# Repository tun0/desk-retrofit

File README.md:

# Jysk Slangerup standing desk — smart drive retrofit

Reverse engineering notes, design decisions and firmware for replacing the
control of a **Jysk Slangerup** electric height-adjustable desk.

The original complaint: the up/down buttons switch the motor on at full
voltage, so the desk jolts into motion. The goal is soft start/stop under
programmatic control, with height presets as a later phase.

This document is the project's memory. It records not just the final design
but the measurements it rests on, the alternatives considered, and — deliberately —
the wrong turns, because several conclusions here are only correct in light of
an earlier mistake.

---

## 1. The desk as found

### 1.1 Documented facts

From the JYSK manual (rev. 1, 22.06.2022; item numbers 3601130, 3601131,
75668001, 75672001, C123681):

| Property | Value |
|---|---|
| Height range | 68–118 cm |
| Max load | 40 kg |
| Speed | ~25 mm/s, load dependent |
| Duty cycle | 10% at 50% max load, or 2 min continuous |
| Operation | Micro switches |
| Anti-collision | **Not listed** (JYSK's SVANEKE model does advertise it) |
| Manufacturer of record | 2-connect ApS, Ikast, Denmark |

Essentially nothing else is publicly documented. 2-connect is a furniture
trading and sourcing company rather than an electronics designer, so they are
the CE-responsible party and the parts are unbranded OEM. There is no control
box model number, no wiring diagram, no service manual, no aftermarket
replacement. The Machinery Directive technical file is only available to
national market-surveillance authorities, not the public.

**Conclusion: everything below was measured, not looked up.**

### 1.2 Physical layout

- **Single motor**, permanently attached to one leg, driving the second leg
  through a shaft. Both columns are mechanically locked together, so one
  position measurement is authoritative for the whole desk.
- **No separate control box.** The electronics — such as they are — live in
  the motor housing. Only two cables exist: PSU → motor housing, and a
  4-conductor cable between the motor housing and the handset.
- The handset enclosure contains two rocker microswitches and nothing else.

### 1.3 Power supply

Label reads:

```
Input:  AC 100-240V  50/60Hz  1.5A
Output: DC 29.0V  1.8A  52.2W
```

The 1.8 A rating turns out to be one of the most important numbers in the
project — see §2.4.

### 1.4 The 4-conductor cable

Terminals on the motor housing, left to right: **red, yellow, white, grey**.

| Conductor | Connects to |
|---|---|
| red | UP rocker only |
| yellow | both rockers |
| white | both rockers |
| grey | DOWN rocker only |

Two shared conductors, one unique conductor per rocker, three terminals per
rocker. That topology is the signature of **two SPDT changeover switches
sharing a common pair** — the minimal H-bridge you can build from two rockers.

### 1.5 The connector

**Molex Mini-Fit Jr., 4.20 mm pitch, 4 circuits, dual row (2x2).**

Identified by caliper, recorded here because the pitch is genuinely awkward to
measure on a moulded housing with recessed cavities, and a first attempt at
buying an extension cable got the wrong part.

Two measurements, and how they combine:

| Measurement | Value |
|---|---|
| Terminal centre-to-centre (pitch), approximate | ~4 mm |
| Outer edge to outer edge across two adjacent cavities | 7.7 mm |

The second is the reliable one — flat outside faces, a longer span, so a
smaller relative error. It equals **one pitch plus one cavity width**:

```
7.7 mm  =  4.2 (pitch)  +  3.5 (cavity)      → Mini-Fit Jr.   ✓
5.4 mm  =  3.0 (pitch)  +  2.4 (cavity)      → Micro-Fit 3.0  ✗
```

Micro-Fit was the initial guess — it is the usual choice for this class of
desk — but it cannot produce a 7.7 mm span. For reference, a Micro-Fit 3.0
dual-row 4-circuit part measures 9.65 mm along the row axis against 6.65 mm
for the 2-circuit version; the 3.00 mm difference is exactly one pitch.

Family identification by pitch, for future reference:

| Pitch | Family | Current/circuit |
|---|---|---|
| 2.00 mm | Milli-Grid | low |
| 2.50 mm | Nano-Fit | ~6.5 A |
| 3.00 mm | Micro-Fit 3.0 | 5.0 A |
| 3.50 mm | Ultra-Fit | ~9 A |
| **4.20 mm** | **Mini-Fit Jr.** | **9.0 A** |

9 A per circuit is wildly over-specified for 1.8 A — normal for a furniture
OEM buying whatever was cheap and available.

Quick sanity check without calipers: Mini-Fit Jr. *is* the ATX family. The
4-pin 12V CPU plug on any PC power supply is the same connector.

### 1.6 Pinout and polarity

Measured on the **5557 receptacle** — the half with the *movable* thumb latch,
holding female sockets. The 5559 plug has the fixed catch that latch grabs.

```
Receptacle (5557, female sockets, movable latch)
viewed INTO the mating face, latch uppermost:

        ─── latch ───
      ┌───────────────┐
      │  [ 1 ] [ 2 ]  │   motor pair
      │  [ 3 ] [ 4 ]  │   supply pair
      └───────────────┘

  1 = motor          3 = supply +
  2 = motor          4 = supply -
```

The plug, viewed into *its* mating face, is the left-right mirror of this.
Never carry a "left and right" description across from one half to the other.

> **This numbering matches Molex's own, confirmed against the real sales
> drawing (SD-5557-003, also cited in `NETLIST.md` for the symbol pin
> order).** Its "CIRCUIT SIZE LAYOUT" table shows circuits 1/2 in the row
> nearest the latch and 3/4 in the row away from it, viewed into the mating
> face with the latch uppermost — the identical reference frame and
> assignment used above. The housings themselves still carry no legible
> moulded numbers, so this was derived from the drawing's orientation
> reference, not read off the part; a pre-made cable assembly could still
> use different circuit numbers internally, so don't assume one matches
> without checking.

Even with the numbering confirmed, **mark the connector physically**: a
dab of paint or nail varnish on the MOT_A cavity. Then the
mark is the definition and no orientation reasoning is ever needed again. The
housings are polarised, so the box itself cannot be mated the wrong way round.

**Polarity, measured:**

| Applied | Result |
|---|---|
| 3→2 and 4→1 (circuit 2 positive) | **UP** |
| 3→1 and 4→2 (circuit 1 positive) | **DOWN** |

**Naming convention used throughout this project:**

> **MOT_A** is the conductor that must be **positive to raise** the desk =
> circuit 2.
> **MOT_B** = circuit 1.

Defining it this way makes the schematic correct by construction, so the only
project-specific fact to remember is which circuit MOT_A is.

**On wire colours — not needed.** The colours in §1.4 did one job: deriving
the rocker topology. Everything downstream works in circuit numbers, because
the box mates with connectors rather than cutting into the cable, so a
conductor's colour mid-run never comes up. The connector end also carries a
moulded protector sleeve, so the colours are not visible there anyway.

For the record, the mapping is *predicted* but unconfirmed: red is the UP
rocker's common and the rockers rest on NC → V+ (§2.4), so red goes negative
while raising, making **red = circuit 1 (MOT_B)** and **grey = circuit 2
(MOT_A)**. If it is ever wanted, it can be had without opening the handset:
the colours are visible at the motor housing terminals, so continuity from a
housing terminal to a connector pin gives the mapping with the cable still
installed.

**Re-identification recipe.** The numbering is a convenience, not a
dependency — every fact above is re-measurable in about five minutes with
nothing but a multimeter:

| Step | Measurement | Tells you |
|---|---|---|
| 1 | ~2.5 Ω across a pair | that pair is the motor winding |
| 2 | ~29 V across the other pair (powered) | supply pair; DC volts gives + and − |
| 3 | Park at the **bottom** stop, diode mode across the motor pair | the conductor reading ~0.6 V with the **red** probe on it is **MOT_A** (positive raises) |

Step 3 works because at the bottom stop the limit switch is open and its
bypass diode passes only the escape direction, which is up.

---

## 2. Measurements and what each proved

Every measurement below was taken with mains disconnected unless noted.

### 2.1 Which pair is which

With the handset assembly disconnected:

- ~**30 V** across one pair → these are the supply rails, routed up to the handset.
- ~**2.5 Ω** across the other pair → this is the motor winding, routed up and back.

A relay coil at 29 V would read hundreds of ohms to low kilohms. 2.5 Ω can
only be a winding. **This proved the rockers carry full motor current and that
no controller exists anywhere in the desk.**

### 2.2 Isolation

- Supply negative to either winding terminal: **< 1 V**, and **open** on the
  resistance range.
- All conductor combinations open except the 2.5 Ω winding pair.

This ruled out either winding end being permanently tied to a rail — which
would have shorted the supply on the first press of a naive H-bridge retrofit.

### 2.3 End stops

Diode mode across the winding pair, measured at the motor-side terminals:

| Position | Reading |
|---|---|
| Mid-travel | near zero both directions (the winding) |
| Bottom stop | **0.6 V one way, OL the other** |
| Top stop | same behaviour, mirrored |

This identifies **diode-bypassed limit switches** — a normally-closed
microswitch at each end of travel with a diode across it, in **series** with
the winding. At a limit the switch opens: one polarity is blocked entirely,
the other passes through the bypass diode so the desk can drive away from the
stop. Two switches, two diodes, still only two conductors down the leg.

Consequences:
- The desk cannot be driven past either extreme, in hardware, regardless of
  firmware. This is inherited for free by any retrofit.
- Homing is clean: drive down until current collapses to zero. That is the
  switch opening at a repeatable mechanical position.

### 2.4 Rest state and current

With both rockers in neutral, **three of the four contacts read shorted**, to
the **positive** rail. Both rockers sit on their NC contacts, tying both
winding ends to V+. That is dynamic braking, and it explains why the desk
stops as abruptly as it starts.

Locked-rotor current would be 29 V ÷ 2.5 Ω ≈ **11.6 A** — but the supply is
rated 1.8 A. The PSU current-limits long before the winding sees anything like
that. Practical consequences:

- The supply is already acting as the current limiter and, incidentally, as
  the collision protection. Jam the desk and it drops into limit and stalls
  rather than drawing 12 A.
- **Do not casually fit a bigger PSU.** That current limit is load-bearing
  safety on a frame with no other protection, and the motor's thermal rating
  was chosen around it.
- A sanity check supports this: lifting ~60 kg at 25 mm/s is ~15 W mechanical,
  which through a spindle drive lands near 40–50 W electrical. The desk runs
  close to the supply limit under load, which is exactly what the manual's
  "speed depends on load" is describing.

### 2.5 The as-found circuit

```
SW3 (UP rocker, SPDT):
    NC ── V+
    NO ── V−
    COM ── [LIM_top ∥ D_down] ──┐
                                 │
                                (M)
                                 │
SW4 (DOWN rocker, SPDT):         │
    NC ── V+                     │
    NO ── V−                     │
    COM ── [LIM_bot ∥ D_up] ─────┘
```

At rest both rockers sit on NC (→ V+), tying both winding ends to the
positive rail — that's the brake state. Pressing a rocker moves its COM
to NO (→ V−) instead, which is what drives the motor.

Not kept as a separate schematic file — this circuit is fully captured by
the measurements above and the diagram, and the stock wiring is unmodified
in the chosen design (§4).

---

## 3. Design evolution

Four designs were considered in sequence:

| | Design | Outcome |
|---|---|---|
| 3.1 | ESP32 + integrated H-bridge IC | rejected on voltage headroom |
| 3.2 | Relay direction + low-side FET PWM | adopted as the drive topology |
| 3.3 | In-line interceptor with 3-pole transfer relay and automatic fallback | good design, dropped as over-complex |
| 3.4 | **Simple in-line drive** | **chosen** |

> Why each of the first three lost, and what would be worth keeping if any
> were revived, is in **`APPENDIX.md` §5**. Several were reasonable at the time
> and became obsolete only when a later measurement changed the picture.

### 3.4 Simple in-line drive — **CHOSEN**

Same in-line position, no transfer relay, no automatic fallback. The board
owns the winding permanently. Reverting is physical:

```
motor — box — handset      becomes      motor — handset
```

39 components instead of 51. Dropping the transfer also deleted the clamp
diodes: with no transfer relay, 29 V can never appear on the handset
conductors, so there is no transition window to protect against.

---

## 4. The chosen design

Schematic: `desk.kicad_sch` / `.pdf`.

### 4.1 Topology

```
PSU 29V ────────┬── VSW rail
                │
                ├── buck ── +5V ── ESP32
                │
         [K1]───┴────[K2]        two SPDT relays, NC→VSW, NO→MRET
          │           │
          └─ winding ─┘      via limit switches in the leg
                │
              MRET ──[Q5]── GND    low-side PWM
                │
              [D1] freewheel to VSW
```

### 4.2 Relay truth table

`MOT_A` = circuit 2, positive to raise (§1.6). `MOT_B` = circuit 1.

| K1 | K2 | Result |
|---|---|---|
| off | off | both winding ends on VSW → **brake** (matches OEM rest state, and is the boot state) |
| **on** | off | MOT_B to return, MOT_A stays positive → **UP** |
| off | **on** | MOT_A to return, MOT_B stays positive → **DOWN** |
| on | on | both ends on MRET → coast if Q5 off, brake to ground if on |

No combination shorts the supply.

The signal chain therefore runs `DIR_A → U3 → Q3 → K1 = up` and
`DIR_B → U3 → Q4 → K2 = down` (same chip, different gate units - see
NETLIST.md), which is what `relay_up:` and `relay_down:` in
`desk.yaml` are wired to. The current sensor sits in the K1 (MOT_B) leg; either
leg works, since it only needs to be inside the freewheel loop.

### 4.3 The handset

Permanently removed from the motor circuit. The board feeds it **3.3 V** and
reads the rockers as dry contacts — high at rest through the OEM NC contact,
low when pressed. Same cable, same connectors, different job. The tactile
up/down survives alongside the screen.

### 4.4 Current sensing

An **ACS712ELCTR-05B** sits in the motor leg, *not* in the FET return (switched
from the ACS724-5AB this design used earlier — see §6.5/§6.6; same Hall-effect
family, pin-identical, chosen for real stock availability). With low-side
chopping the FET only carries current during the on-time; freewheel current
bypasses it entirely, so a low-side shunt would read a chopped fraction and
need synchronous sampling. In the motor leg the sensor is inside the freewheel
loop and reads true motor current continuously.

Its output is centred at 2.5 V, 185 mV/A (Allegro's own datasheet figure for
this exact part), reaching ~3.4 V at the full ±5 A range - over a comfortable
ADC margin, so R1/R2 (10k/20k) divide it down to a ~2.3 V max. **ISENSE must
be on ADC1** — ADC2 is unusable while WiFi is active.

### 4.5 Failsafe layer

- **Boot state.** R8/R9/R10 hold all three drive lines at "off" before firmware
  runs. These *must* sit on non-strapping GPIOs — on the classic ESP32 avoid
  GPIO0, 2, 12 and 15, since a pull resistor there fights the bootloader and
  GPIO12 pulled high selects the wrong flash voltage. The S3's strapping set
  differs; the principle holds.
- **Watchdog.** A 74HC123 retriggerable monostable (~250 ms) gates all three
  drive lines through a 74HC08. The ESP32 must keep kicking it. This sits
  **downstream of the MCU** deliberately: LEDC PWM keeps running in hardware
  after a firmware hang, so stopping PWM in software is not a safety measure.
- **Sequencing.** Relays change state only with Q5 off and current decayed
  (~50 ms). Switching contacts under a couple of amps of inductive DC is how
  relays weld, and a welded direction relay on a desk is a genuinely bad
  failure. On a watchdog trip this holds automatically: Q5 turns off in
  microseconds while relays take milliseconds to release.
- **Coast is safe.** Loss of drive leaves the desk where it is, because the
  spindle is self-locking. This is why the stock desk isn't dangerous despite
  having no electronics at all.
- **Duty cycle.** Enforce the manual's 10% / 2-minute limit in firmware.
  Thermal damage is the boring failure mode.
- **Travel timeout.** Full range is 500 mm at 25 mm/s, so anything over ~25 s
  of continuous drive is a fault.

---

## 5. Corrections made along the way

Recorded because several later conclusions only make sense in light of these.

1. **"No anti-collision implies no current sensing."** Too quick. If the desk
   had used stall detection at the end stops, it would have needed current
   sensing after all. Resolved by finding passive diode-bypassed limit
   switches — but the inference was unsound until then.
2. **Predicted the wrong diode-test result.** Expected "winding one way, diode
   the other". Wrong: the switch and its bypass sit in *series* with the
   winding, so at a limit one polarity is blocked entirely. The measured
   0.6 V / OL is what the series arrangement predicts.
3. **Recommended BTS7960 / VNH5019 on current headroom alone.** Both are out
   of voltage spec at 29 V (BTS7960: 5.5–27.5 V; VNH5019: 5.5–24 V). They
   survive 40 V+ as absolute maximum, but "probably fine" is not what should
   be holding up a desk.
4. **"Size the bridge for 12 A stall."** Wrong — the PSU current-limits at
   1.8 A, so the winding never sees locked-rotor current. This also reframed
   the supply as the existing collision protection.
5. **"Losing brake removes protection."** Overstated, and inconsistent with
   the self-locking spindle noted elsewhere. The brake does stop-precision
   work, not safety work.
6. **Wired NC to V− in the first `desk_original` schematic.** The measurement
   (three contacts shorted, to the positive rail) says NC → V+. Caught only
   when the netlist was rendered as a connectivity graph; the written note and
   the drawing had disagreed silently.
7. **Ran literal power rails across the schematic sheet.** Intended to remove
   "islands"; produced a picket fence of metre-long ground verticals instead.
   Local GND and rail symbols are the conventional idiom precisely because
   they avoid this. The real problem was that *signals* were labelled rather
   than wired.
8. **Planned an "ESP32 devkit + display" (CYD).** This board lives under the
   desk, not somewhere a display is ever seen, so U1 is a bare
   ESP32-S3-DevKitC instead. A display, if ever wanted, would be a separate
   peripheral mounted on the desk itself, not part of this board.
9. **Specified Q5 as IRLB8721.** Caught by an external review, not by this
   project's own process — the schematic still had it after the part was
   supposedly already swapped. IRLB8721's 30 V VDSS doesn't clear the 29–30 V
   rail once flyback clamping is accounted for; fixed to IRLZ44N (55 V). See
   §6.2.
10. **Assumed hand-wired perfboard was the assembly plan.** Reasoning at the
    time: this design is all through-hole specifically because there's no
    reflow equipment, and a fab-house PCB order felt like overkill for a
    one-off — so point-to-point perfboard wiring, guided by a generated
    wiring table, looked like the natural fit. Reversed once that wiring
    table turned out to need far more jumpers than expected, concentrated
    around locally dense ICs rather than anything structural — a strong
    signal that hand-wiring reliability, not layout, was the actual risk.
    A real 2-layer board (still hand-soldered, still through-hole — see
    §6.5) routes those same nets with zero jumpers once an autorouter can
    place traces on both layers, so it was worth doing even without a
    fab-house order: milled at home from a standard 70×100mm pre-cut
    copper-clad blank instead of ordered or hand-wired. See
    `schematics/desk.kicad_pcb` and its commit history for the design
    itself.
11. **Rejected pcb2gcode on hearsay, never actually tested it.** An earlier
    session ruled it out from other people's reported experiences and
    settled on FlatCAM instead (`schematics/gen/mill.tcl`). Building
    increasingly rigorous isolation-milling verification tooling
    (`verify_isolation.py`) around FlatCAM's output eventually surfaced
    three distinct, confirmed FlatCAM `isolate()` bugs on this board's
    ground-pour-heavy layout — including one (a G-code path-ordering
    detour that silently skips a short loop-closing segment) that isn't
    patchable in general. Trying pcb2gcode directly (after working around
    a stale AUR package — see APPENDIX §7) found it isolates this board
    measurably more completely, with no equivalent defect found. The
    milling pipeline defaulted to pcb2gcode (`make mill`) for a while; the
    FlatCAM pipeline stayed in the repo as an explicit fallback
    (`make mill-flatcam`) since pcb2gcode needed a from-source build. See
    APPENDIX §7 for the full technical investigation.
12. **Assumed a third-party isolation-routing tool was necessary at all.**
    Trying pcb2gcode's own `--voronoi` mode (to clean up some harmless but
    untidy leftover copper) surfaced two more real bugs - one of them an
    actual short, not just cosmetic. That's five confirmed bugs across two
    independent tools' internal polygon-offset algorithms, and zero in
    KiCad's own zone fill. `schematics/gen/custom_isolate.py` generates the
    isolation toolpath directly from that same already-correct KiCad
    boundary (the SVG render `verify_isolation.py` already trusted as
    ground truth) using Shapely/GEOS - a mature, heavily-used library
    specifically because robust polygon offsetting is hard to get right,
    which is exactly where FlatCAM and pcb2gcode's own implementations kept
    failing. Extensive spot-checking (all four mounting holes, a full
    header row, several vias and a thermal-relief pad) found no bugs in it.
    Now the default `make mill`; pcb2gcode and FlatCAM both stay as
    explicit fallbacks (`make mill-pcb2gcode`, `make mill-flatcam`). See
    APPENDIX §7.2 for the full investigation.
13. **`island_removal_mode=Never` on both GND pours, inherited unchanged
    into the fab-manufacture exploration.** That setting was deliberate for
    milling (cheaper to leave a disconnected fill fragment as solid copper
    than carve bare board around it for no electrical reason) -
    `schematics/gen/reroute_pcb.py`'s own comment says so. It has no reason
    to survive on `pcb-fab-redesign`: a fab house's etch cost doesn't
    depend on how much copper is removed, so those fragments were just
    isolated, non-functional copper labelled GND without being connected to
    it. Flipped to `Always` and refilled; DRC unaffected (same 20
    pre-existing silkscreen warnings, nothing copper-related).

This branch exists to explore manufacturing the board at a fab house
instead of hand-milling it, after the milling investigation above (and the
calibration coupons in `schematics/gen/feedrate_stresstest.py` /
`tracknet_stresstest.py`) made clear how much of the schedule and risk
budget the milling step was consuming. Going to a fab removes that risk
entirely - the design's actual DRC clearance (0.4mm, `desk.kicad_pro`) is
already well inside any commercial 2-layer fab's capability (≤0.15mm is
routine), so no design-rule loosening is needed, and it frees up decisions
that were previously constrained by the mill/jig process: the ground pour
can stay (or even improve, now that isolated fragments are gone), and
component/connector placement (e.g. screw-terminal orientation) is no
longer constrained by hand-mill registration. Main trade-off: cost and
lead time (small-batch 2-layer boards are cheap, but typically a ~5-board
MOQ and 1-2 weeks) replace milling's slow-but-immediate turnaround. No
decision has been made yet - this is why it's a branch, not a change to
the chosen design in §4.

---

## 6. Bill of materials

Rough EUR incl. BTW, Netherlands. Prices are budgeting figures, not quotes.

| Item | Note | Cost |
|---|---|---|
| ESP32-S3-DevKitC | bare devkit, no display — see §5 | €5–15 |
| 2x SRD-05VDC-SL-C relay | bare relay, not a driver-included module — this design drives the coil directly, see NETLIST.md Drive section | €3–5 |
| 2x 2N7000 MOSFET | relay coil drivers (Q3/Q4), TO-92 — through-hole | €1–2 |
| IRLZ44N MOSFET | logic-level, 55V — see §6.2 | €1–2 |
| BC337 + BC327 | discrete gate driver push-pull — see §6.2 | €1–2 |
| 74HC123 + 74HC08 | watchdog and gating | €1–3 |
| SB560 Schottky | freewheel | <€1 |
| 2x 1N4148 | relay coil flyback diodes (D2/D3), DO-35 | <€1 |
| ACS712ELCTR-05B (bare) + SOIC-8→DIP-8 adapter | bidirectional, 5A — see §4.4/§6.5; switched from the ACS724xLCTR-05AB this design used earlier for real stock availability (pin-identical, see §6.6); the Pololu carrier is dropped either way, its 2 caps (C2/C3) now on the main board instead; or 10 mΩ shunt + INA240, similar cost | €2–5 |
| LM2576HVS-5.0 buck | **must** be the true HV variant (60V input) — see §6.1/§6.5; SMD (TO-263-5), not the THT part this design used earlier, which proved unsourceable at hobbyist quantities | €6–9 |
| TVS 33 V bidirectional | D4 — no fuse fitted, see §6.1 | <€1 |
| Passives | resistors, caps | €4–8 |
| 4x 2-position screw terminal | 2.54mm pitch, board-side termination (TB1, TB2, TB4, TB5) — see §6.4 | €2–4 |
| Mini-Fit Jr. housings + terminals | 2 mating pairs, each now on a short pigtail off the board rather than a board-mount connector — see §6.4 | €3–6 |
| PCB blank, 70×100mm pre-cut copper-clad (2-layer) | milled, not fab-house ordered — see §6.5; SHOPPING_LIST.md flags this as still needing a specific supplier | €5–10 |
| **Total** | | **€25–100** |

Phase 2 adds ~€15–25 for a VL53L1X carrier and bracket. Sourcing detail
below (§6.6).

### 6.1 Voltage, not current, is the constraint

The rail is 29 V nominal, 30 V unloaded. Anything in the motor path or the
buck input needs headroom above that. Common traps:

- BTS7960 / IBT-2: spec'd 5.5–27.5 V. Out of spec.
- VNH5019: 5.5–24 V. Out of spec.
- MP1584 / Mini-360 buck modules: top out ~28 V. Marginal at best.

No fuse is fitted (there was one in early drafts, `F1`). The wall supply
already current-limits at 1.8 A — that limit is this design's only collision
protection, already relied on elsewhere (§4.4, `CLAUDE.md`'s own hard
invariants) — so a fuse adds little on top of it while being one more
embedded part to replace if it ever blows. The OEM desk never had one
either. D4 (33 V bidirectional TVS) stays.

### 6.2 Q5: voltage rating first, then the gate driver

**Q5 is IRLZ44N (55 V), not IRLB8721 (30 V).** The IRLB8721 is a common
default for "logic-level MOSFET," but its 30 V VDSS doesn't clear this
29 V nominal / 30 V unloaded rail — at PWM turn-off the freewheel diode
clamps the drain to VSW plus a diode drop, putting it at or over absolute
maximum every cycle. Substitution criterion for any replacement: check
**Qg and VDSS**, not Vgs(th) — plenty of parts marketed as "logic-level"
still top out at 30 V.

The gate driver still isn't optional: at 3.3 V Vgs a logic-level MOSFET is
only partially enhanced, and at 20 kHz that's how you cook a part that
would otherwise dissipate under 0.1 W. This design drives Q5 from a
discrete BC337/BC327 push-pull (not an IC — see `schematics/gen/symbols.py`),
fed 5 V through the AND gate output. Avoid the ubiquitous IRF520 "MOSFET
trigger" modules — that FET isn't logic-level at all.

### 6.3 K1/K2 are bare relays, not a driver-included module

**This design drives the coil directly** (Q3/Q4 discrete transistor
switches, D2/D3 flyback diodes — see NETLIST.md's Drive section), not
through a prebuilt "2-channel relay module" board. Those Arduino-kit
modules already include their own opto-isolated input, driver transistor
and flyback diode, which would make Q3/Q4/D2/D3 redundant rather than
complementary if one were used here — don't substitute one in without
also removing this board's own driver circuit. What to check when buying
the bare relay itself:

- **Coil voltage** — must be 5 V; this design's coil drive assumes it, and
  a 12 V coil would draw roughly half the current for the same drive
  voltage, undersaturating the relay.
- **Contact rating** — typically 10 A 250 VAC / 10 A 30 VDC. Your 29 V is right
  at that DC limit; acceptable only because contacts are cold-switched
  (§Sequencing/hard invariants — relays only change state with the FET
  off and current decayed).
- **Pinout** — EN50005/"Form C" (the real Kicad symbol this design uses,
  `Relay_SPDT`) is the common footprint for this class of relay; verify
  before assuming a drop-in substitute matches pin-for-pin.

### 6.4 Connector parts (Mini-Fit Jr., 4 circuit dual row)

| Part | Molex no. | Legacy |
|---|---|---|
| Receptacle housing (holds female terminals) | `39-01-2040` | 5557-04R |
| Plug housing (holds male terminals) | 5559 series, 4-circuit | 5559-04P |
| Female crimp terminal | 5556 | |
| Male crimp terminal | 5558 | |

**Wire-to-wire pairs a 5557 receptacle with a 5559 plug.** Datasheets for the
5557 list 5566 and 5569 as mating housings — those are *PCB headers*, not the
wire-to-wire half. That is the most likely explanation for the first wrong
order, alongside Molex's naming: a "receptacle housing" holds female terminals
while a "plug housing" holds male pins, and the plug is the part that inserts
into the receptacle. Order by the terminals, not by the shape you are looking
at, and check the datasheet drawing.

The retrofit box needs a **5559 plug on one end and a 5557 receptacle on the
other**, so it drops into the existing cable run in only one orientation.

Make up a short 5557-to-5559 **coupler** at the same time and tape it inside
the leg. That is the one-minute revert, and it is worth doing while the parts
and crimp tool are already on the bench rather than at an awkward moment.

Because this is the ATX family, a PC 4-pin 12V CPU extension is mechanically
correct and costs a few euros. Two cautions: verify the pinout is
straight-through 1:1 rather than crossed, and PC cables use stiff 18 AWG that
may not sit well in a desk-sized strain relief. Crimping your own in 20 or
22 AWG gives a tidier result; 2 m at 1.8 A is a couple of hundred millivolts
round trip either way.

Build any extension by **matching wire colours end to end** rather than
trusting circuit numbering. One reversed pair swaps the rails.

**The board itself doesn't carry a Mini-Fit connector at all.** Each side
(motor housing, handset) terminates on the board in a 2-position screw
terminal instead (TB1, TB2, TB4, TB5 — 2.54mm pitch, solders straight onto perfboard,
no crimp tool needed for board assembly). A short pigtail, crimped
separately on the bench, carries each pair from its screw terminal to the
actual Mini-Fit half (still needed, still built exactly as described
above) that mates with the cable. One extra connection point per circuit
versus terminating the Mini-Fit directly at the board edge, traded for
never needing a crimp tool during board assembly or rework.

### 6.5 This design is deliberately all through-hole

A hand-soldered, self-milled 2-layer PCB (`schematics/desk.kicad_pcb`,
sized to a standard 70×100mm pre-cut blank), not a fab-house order and not
raw perfboard either — but the reason for through-hole-only still holds
regardless of which of those three it ends up being: no reflow equipment.
Every substitution should preserve that, not just match electrically.
Substitution criterion is the **package**, not just the part:

| Part | Through-hole option |
|---|---|
| 74HC123 | `74HC123N` / `SN74HC123N`, DIP-16, socketed |
| 74HC08 | `SN74HC08N`, DIP-14, socketed |
| BC337 / BC327 | TO-92 (already through-hole) |
| IRLZ44N | TO-220 |
| 2N7000 | TO-92 |
| SB560 | DO-201AD axial |
| TVS 33 V | `P6KE33CA` or `1.5KE33CA`, axial |
| Coil flyback | `1N4148`, DO-35 |
| SRD-05VDC-SL-C relay | bare relay, TO-5-ish THT (EN50005/Form C) |
| ACS712 | bare SOIC-8 chip on a generic SOIC-8→DIP-8 adapter, socketed like U1 |
| ESP32-S3-DevKitC | devkit module, socketed with 0.1" pin headers |

Every DIP part on this board is socketed, not just U1/U4 as originally
planned - noticed missing from the shopping list only after seeing a
render (see conversation), added for all of U2/U4/U3 once caught. Worth
it specifically because this board is hand-milled, not a plated-through-
hole fab board - pads are more fragile under a desoldering mistake here
than on a normal PCB, and sockets cost pennies.

**U5 (buck regulator) is the one deliberate exception.** The true
through-hole HV buck (`LM2596HVT`/`LM2576HVT`, TO-220-5) turned out to not
practically exist at hobbyist quantities anywhere checked — Reichelt, TME,
Mouser, Farnell direct, and Farnell-via-sinuss.nl all came up empty or
unconfirmed for the T-suffix part specifically (see conversation). The
real, in-stock option is `LM2576HVS-5.0/NOPB`, S-suffix, **TO-263-5 SMD**.
This doesn't violate the "no reflow" reasoning, though: TO-263-5 is 5
large gull-wing leads at roughly TO-220 pitch plus a thermal tab, one of
the more hand-solder-friendly SMD packages that exists — no hot air or
reflow needed, just a bit more dwell time on the tab. Checked directly
against TI's own datasheet: TO-220-5 and TO-263-5 share an identical pin
table, so this was a footprint-only change, no rewiring.

ACS712 (`ACS712ELCTR-05B`, §4.4) is SOIC-8, not through-hole itself — what
keeps the board through-hole is whatever it's mounted on, same reasoning
as U1. This design used the ACS724xLCTR-05AB before switching to ACS712
(same Hall-effect family, verified pin-identical against both datasheets
directly, pin-for-pin — not assumed from the similar part number or a
misleadingly-named KiCad library symbol, see conversation) purely because
the ACS724 bare chip proved nearly unsourceable, while ACS712ELCTR-05B is
in real stock at three-plus suppliers already in rotation for this
project. Either way, mounting the bare chip on a generic SOIC-8-to-DIP-8
adapter (0.3"/7.62mm row spacing, already in inventory) instead of a
ready-made carrier (Pololu, in this design's earlier revisions) drops two
things that carrier provided for free: a 0.1uF VCC bypass cap and a 1nF
FILTER-to-GND cap, both confirmed against Allegro's own ACS712/ACS724
application circuit (identical circuit on both parts' datasheets, not
just the Pololu board). Both are now discrete parts on the main schematic
instead (C2, C3) - see NETLIST.md.

### 6.6 Sourcing (Netherlands)

Ruled out, with reasons, so they are not re-evaluated:

- **Digikey** — ~€25 shipping on small orders.
- **Farnell direct** — private-customer orders need a write-in request
  (email/fax/post) and prepayment, not normal checkout, on top of the €50
  minimum. **sinuss.nl** is a live, working Farnell/element14 private
  reseller for NL/BE (confirmed directly, unlike muxtronics.nl's own
  Farnell-intermediary service, which is dead) — usable if a Farnell-only
  part is unavoidable, but at a real price premium (30–50%+ over Farnell's
  own business pricing, confirmed directly) - not worth it for anything
  also stocked at Reichelt/TME.

Working pattern, per actual checked availability (see conversation for
the full supplier-by-supplier matrix):

- **Reichelt** — jellybeans and basic semis: resistors, caps, diodes
  (1N4148, SB560, TVS), 2N7000, IRLZ44N, `74HC123N` (also at Mouser and
  Farnell direct - TME is the actual outlier here, not Reichelt), screw
  terminals.
- **TME** — `SN74HC08N`; the `LM2576HVS-5.0/NOPB` SMD buck (§6.5 - the
  through-hole HV buck isn't practically available anywhere at hobbyist
  quantities); the SRD-05VDC-SL-C's real named equivalent, Omron
  `G5LE-1-5VDC` (5V coil, SPDT/Form-C, 10A/250VAC-30VDC — exact spec
  match, the bare Songle part itself is a module-market item most proper
  distributors don't stock discretely); and `ACS712ELCTR-05B` — confirmed
  in stock by hand after automated checks kept giving contradictory
  stock figures for it. Between this and the buck/relay, TME covers
  enough that **Mouser isn't needed at all** for the current design.
- **Modules** (ESP32 devkit, etc.) — TinyTronics (Ede), Kiwi Electronics,
  Opencircuit (Zaandam) or Antratek.
- **PCB blank** (70×100mm copper-clad) — not found at any of the above;
  expect to need a hobby/eBay/AliExpress source, as originally
  anticipated.

Substitutes worth recording:

- **IRLZ44N** → any 55–60 V logic-level N-channel in TO-220. Check **Qg and
  VDSS**, not Vgs(th) — see §6.2.
- **74HC08** → 74HC00 with inverted logic, or 74HC11 triple 3-input AND.
- **ACS712** → 10 mΩ shunt + INA240 (in the motor leg, not the FET return -
  same reasoning as §4.4), but INA240 is SOIC-8 and needs a breakout too -
  same treatment as ACS712 itself (§6.5), not a way to avoid one.

---

## 7. Firmware

ESPHome, with motion control in a custom external component.

Pure YAML cannot do this safely. Three reasons, all in the safety path:

- The watchdog kick must come from the control loop, not a timer. ESPHome's
  `interval` runs in the cooperative main loop, which WiFi work can stall for
  hundreds of ms. Solving that with a hardware LEDC pulse is worse — it keeps
  kicking through a hang, making the monostable decorative.
- Relay sequencing is a small state machine with real timing constraints.
- `adc` sensors poll on the order of seconds. Useless for collision detection.

What ESPHome earns: OTA, logging, web server, Home Assistant integration, and
LVGL for the screen. Inheriting `cover::Cover` makes the desk a first-class HA
entity with open/close/stop/position and no glue.

### 7.1 Structure

```
config/
  desk.yaml
  my_components/
    desk/
      __init__.py      (empty)
      cover.py         config schema + codegen
      desk_cover.h
      desk_cover.cpp
```

`cover.py` declares the YAML keys and emits C++ setter calls into the
generated `main.cpp`. Anything configurable goes there; anything fast goes in
the `.cpp`.

### 7.2 Control loop

A FreeRTOS task pinned to **core 0**, ticking at 200 Hz via `vTaskDelayUntil`.
WiFi lives on core 1 and cannot stall it. Each tick reads current, runs the
state machine, updates PWM duty, and *then* kicks the watchdog — after a
completed iteration, never on a timer.

States: `IDLE → SETTLING → RAMPING → RUNNING → STOPPING → IDLE`, plus a latched
`FAULT`. Relay writes are legal in `IDLE` only, and every direction change
routes through `SETTLING`. Enforcing that structurally is what stops a future
refactor quietly switching a relay under load.

Starting parameters: 20 kHz PWM, 500 ms ramp up, 300 ms ramp down, 50 ms
settle. Tune the ramps by feel.

### 7.3 To fill in

- `read_current_()` is implemented (both IDF 4.x `adc1_get_raw` and 5.x
  `adc_oneshot_read` paths, selected via `ESP_IDF_VERSION` - see
  `desk_cover.cpp`), but not yet compiled or flash-tested against real
  hardware. Why the YAML specifies `esp-idf` rather than Arduino at all:
  ESPHome's `adc` sensor is far too slow for a 200 Hz control loop.
- Relay `inverted:` flags follow this board's own direct-drive polarity
  (AND-gate through the 2N7000 coil drivers — see §6.3/NETLIST.md's Drive
  section), fixed by this design, not something a swappable module would
  determine.

**Flash with the motor unplugged first.** Watch the log and the current sensor
before anything can move.

---

## 8. Phase 2 — position feedback and presets

Phase 1 deliberately has no absolute position sensing. Presets need it.

> Full option analysis, including mounting constraints, range limits and the
> approaches that will not work, is in **`APPENDIX.md` §2**. The summary below is
> the decision, not the reasoning.

### 8.1 Direction

Leading candidate is a **VL53L1X time-of-flight sensor** aimed at the fixed
foot plate. Absolute encoding is not worth paying for, because the bottom
limit switch already gives a repeatable mechanical reference detected by
current collapse — one trip down re-homes the desk.

> Full analysis — mounting constraints, the range limit that could sink it,
> incremental optical and magnetic alternatives, commutator ripple counting,
> and why an IMU cannot do this — is in **`APPENDIX.md` §2**.

**Board prep done now, ahead of the actual build (see conversation):**
SDA/SCL break out to a real connector, `TB3`, a 5th screw terminal of the
same type as TB1, TB2, TB4, TB5, fully routed and DRC-clean. +3V3/GND for the sensor
don't get their own terminal - land a second wire under each of `TB2`'s
own two screws instead (it already carries +3V3/GND to the handset; check
that this terminal's rising-clamp accepts two wires per screw before
counting on it - a dedicated second terminal, `TB6`, was tried and
dropped once TB2-sharing made it unnecessary).

**SDA/SCL are on GPIO38/GPIO41, not GPIO12/GPIO13.** The original choice
(physical pins 18/19 on U1's footprint) turned out to sit in a part of the
board that's already at real copper capacity - neither Freerouting nor
careful manual routing could get a single track out from there, regardless
of where TB3 sat. GPIO38/41 (physical pins 35/38) sit immediately next to
DIR_A/DIR_B/PWM (pins 36/37/39), GPIOs that already route successfully
from that same neighborhood - moving to them, and relocating TB3 close by
(rotated 90° to fit the only free space in that corner), routed cleanly on
the first attempt after that. Neither is strapping/PSRAM-reserved/native-
USB, same constraints as the original choice. Firmware should target
GPIO38 (SDA) and GPIO41 (SCL) for this reason - not the GPIO12/13 an
earlier version of this section named.

### 8.2 Data worth logging from day one

Current against time for a full travel in each direction, and coast distance
after cutoff at various speeds. That's exactly the calibration data phase 2
needs, and you get it free by using the desk. If commutator ripple turns out
to be cleanly visible on the current-sense trace, the cheapest option may be
the one already built.

---

## 9. Open questions

- Exact position of the limit switches inside the leg is inferred from
  behaviour; the leg was never opened.
- The polarity convention at each limit (which probe orientation gave 0.6 V)
  was not written down. Two-minute remeasure, needed before wiring the relays
  so "up" is actually up.
- Wire colour to circuit number is predicted but unconfirmed (§1.6), and is
  **not required** for the build — noted only for completeness.
- Which of yellow / white is supply positive was never recorded. Also not
  required: circuits 3 and 4 are identified on the connector itself.
- The housings carry no legible moulded circuit numbers, but §1.6's numbering
  is now confirmed against Molex's own SD-5557-003 drawing, not just this
  file. Still worth marking the MOT_A cavity with paint so the physical part
  carries the convention directly, rather than requiring a lookup.
- ERC has been run (`kicad-cli sch erc`): 127 violations, all triaged as
  either documented gaps (unused MCU pins, U2/U3 spare units, SDA/SCL
  pending Phase 2) or artefacts of this design's power-flag/embedded-symbol
  conventions — no structural defects found.

---

## 10. Files

| File | Purpose |
|---|---|
| `APPENDIX.md` | Background, rejected alternatives, phase-2 analysis — not required to build |
| `CLAUDE.md` | Project context for Claude Code |
| `SHOPPING_LIST.md` | Purchase-ready BOM, grouped by supplier — see §6 for the narrative version |
| `schematics/desk.kicad_sch` / `.pdf` / `.svg` | **The chosen schematic design** |
| `schematics/desk.kicad_pcb` | **The chosen PCB layout** — 70×100mm, 2-layer, hand-milled (§6.5) |
| `schematics/NETLIST.md` | Connectivity reference, generated + annotated |
| `schematics/gen/` | Generator and its dependencies — see `CLAUDE.md` |
| `enclosure/shell.scad` / `.stl` | 3D-printable enclosure (single open-bottom shell) — component clearance is an estimate, see the file's own header comment |
| `my_components/desk/` | ESPHome external component |
| `desk.yaml` | Example ESPHome config |

Schematics are KiCad 7 format (`version 20230121`); KiCad 7, 8 and 9 open them.
Symbols are embedded (either hand-drawn or copied from real KiCad libraries),
so there are no external library dependencies at open-time. Regenerate with
`cd schematics/gen && make` (or `python3 sch.py`, then
`kicad-cli sch export pdf ../desk.kicad_sch`).

---

## 11. Safety notes

- Mains lives in the PSU. All work here is on the 29 V side. Do not open the
  supply.
- 29 V will not hurt you, but a dead short across it will make a mess. The
  supply can deliver 1.8 A continuously and rather more from its output
  capacitance.
- The spindle is self-locking and holds the load unpowered. This is what makes
  coast an acceptable failure mode, and it is the single assumption most worth
  re-verifying if the frame is ever changed.
- The 1.8 A supply limit is part of the safety story on a desk with no
  anti-collision. Replacing the PSU with something beefier removes protection
  the design depends on.

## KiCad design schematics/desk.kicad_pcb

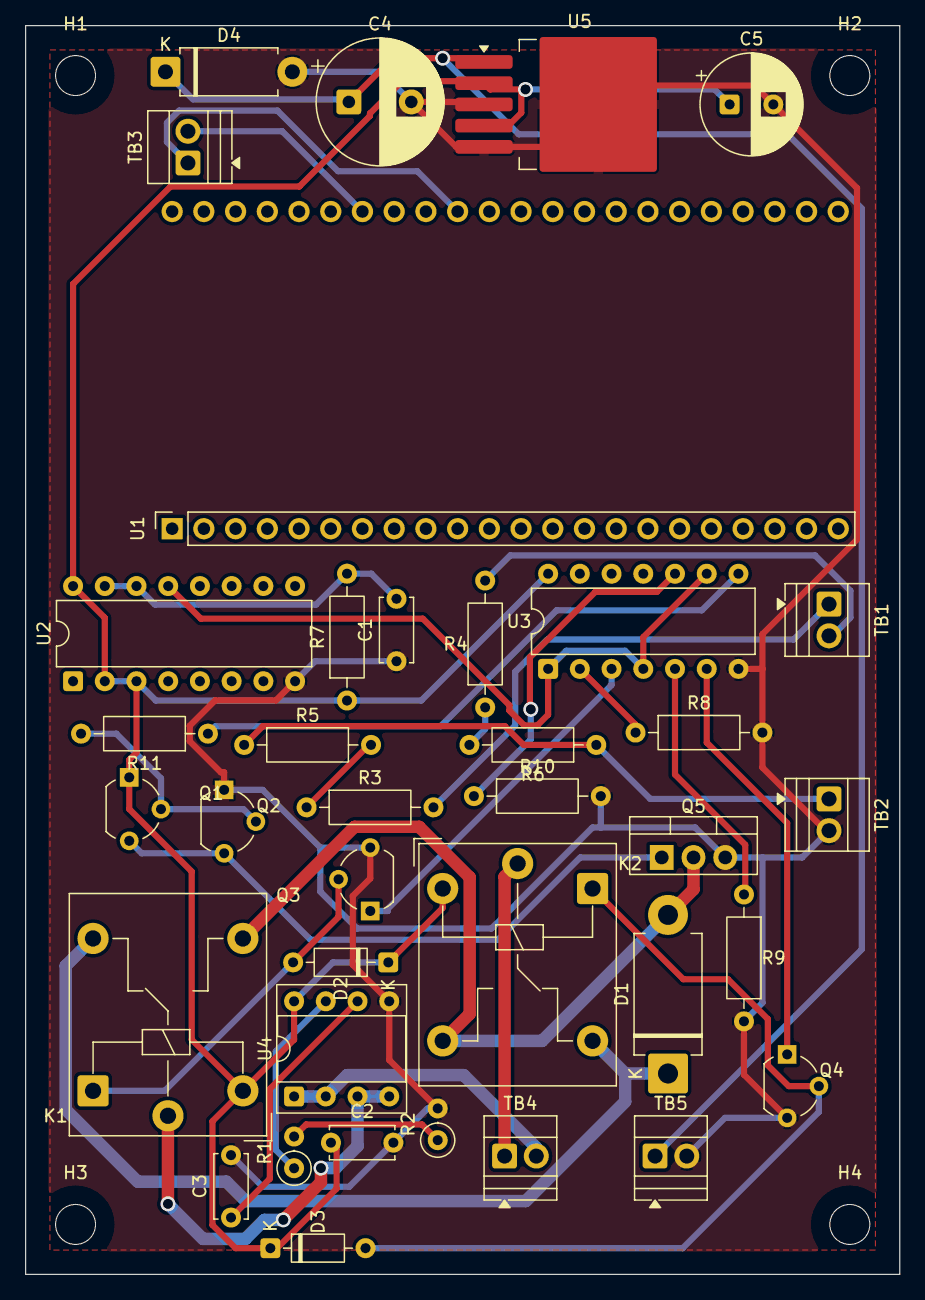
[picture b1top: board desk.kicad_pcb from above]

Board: 2 copper layers, 70.0 x 100.0 mm, 41 parts (0 on the bottom side), 30 nets.

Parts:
C1: 2u2; C_Disc_D5.0mm_W2.5mm_P5.00mm
C2: 100n; C_Disc_D5.0mm_W2.5mm_P5.00mm
C3: 1n; C_Disc_D5.0mm_W2.5mm_P5.00mm
C4: 220u 50V; CP_Radial_D10.0mm_P5.00mm
C5: 220u 10V; CP_Radial_D8.0mm_P3.50mm
D1: SB560; D_DO-201AD_P12.70mm_Horizontal
D2, D3: flyback; D_DO-35_SOD27_P7.62mm_Horizontal
D4: 33V bidir; D_DO-15_P10.16mm_Horizontal
H1, H2, H3, H4: MountingHole_3.2mm_M3
K1: energized = UP (raises desk); Relay_SPDT_Hongfa_JQC-3FF_0XX-1Z
K2: energized = DOWN (lowers desk); Relay_SPDT_Hongfa_JQC-3FF_0XX-1Z
Q1: BC337; TO-92_Wide
Q2: BC327; TO-92_Wide
Q3, Q4: 2N7000; TO-92_Wide
Q5: IRLZ44N; TO-220-3_Vertical
R1: 10k; R_Axial_DIN0207_L6.3mm_D2.5mm_P2.54mm_Vertical
R2: 20k; R_Axial_DIN0207_L6.3mm_D2.5mm_P2.54mm_Vertical
R3, R4: 4k7; R_Axial_DIN0207_L6.3mm_D2.5mm_P10.16mm_Horizontal
R5, R6, R7: 100k; R_Axial_DIN0207_L6.3mm_D2.5mm_P10.16mm_Horizontal
R8, R9, R10: 10k; R_Axial_DIN0207_L6.3mm_D2.5mm_P10.16mm_Horizontal
R11: 1k; R_Axial_DIN0207_L6.3mm_D2.5mm_P10.16mm_Horizontal
TB1: signal pair; TerminalBlock_Xinya_XY308-2.54-2P_1x02_P2.54mm_Horizontal
TB2: power pair; TerminalBlock_Xinya_XY308-2.54-2P_1x02_P2.54mm_Horizontal
TB3: ToF signal pair; TerminalBlock_Xinya_XY308-2.54-2P_1x02_P2.54mm_Horizontal
TB4: motor pair; TerminalBlock_Xinya_XY308-2.54-2P_1x02_P2.54mm_Horizontal
TB5: supply pair; TerminalBlock_Xinya_XY308-2.54-2P_1x02_P2.54mm_Horizontal
U1: DevKitC_2x22_P2.54mm_1in_row
U2: 74HC123 250ms; DIP-16_W7.62mm
U3: 74HC08; DIP-14_W7.62mm
U4: ACS712ELCTR-05B; DIP-8_W7.62mm_Socket
U5: LM2576HVS-5.0 29V-5V; TO-263-5_TabPin3

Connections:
+3V3: R5.1, R6.1, TB2.1
+5V: C2.1, C5.1, D2.1 (K), D3.1 (K), K1.A2, K2.A2, Q1.1, R7.1, U2.2 (B), U2.3 (Clr), U2.16 (VCC), U3.14 (VCC), U4.8, U5.2, U5.4
/DRV_UP: K1.11, U4.3, U4.4
/MRET: D1.2 (A), K1.14, K2.14, Q5.2 (D)
/WDOG: U2.13 (Q), U3.1, U3.4, U3.9
DIR_A: R8.1, U3.2
DIR_B: R9.1, U3.5
GND: C1.1, C2.2, C3.2, C4.2, C5.2, D4.2, Q2.1, Q3.3, Q4.3, Q5.3 (S), R2.2, R8.2, R9.2, R10.2, TB2.2, TB5.2, U2.8 (GND), U3.7 (GND), U4.5, U5.3, U5.5
ISENSE: R1.2, R2.1
unnamed: D2.2 (A), K1.A1, Q3.2
unnamed: D3.2 (A), K2.A1, Q4.2
unnamed: Q1.3, Q2.3, Q5.1 (G)
unnamed: Q3.1, U3.3
unnamed: Q4.1, U3.6
unnamed: Q1.2, Q2.2, R11.2
unnamed: R11.1, U3.8
unnamed: K2.11, TB4.1
unnamed: TB4.2, U4.1, U4.2
unnamed: C4.1, D4.1, TB5.1, U5.1
unnamed: R3.2, TB1.1
unnamed: R4.2, TB1.2
unnamed: C1.2, R7.2, U2.14 (Cext), U2.15 (RCext)
unnamed: C3.1, U4.6
unnamed: R1.1, U4.7
PWM: R10.1, U3.10
SCL: TB3.2, U1.38
SDA: TB3.1, U1.35
SW_DN: R4.1, R6.2
SW_UP: R3.1, R5.2
VSW: D1.1 (K), K1.12, K2.12

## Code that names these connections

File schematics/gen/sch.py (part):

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# longer being on this PCB): avoid strapping (0/3/45/46), avoid this
# module's flash/PSRAM-reserved range (22-37 - wider than usual since
# this is an N16R8/octal-PSRAM part), avoid native USB (19/20), keep
# ISENSE on an ADC1-capable pin.
SIGNAL_GPIO = {"KICK": 4, "ISENSE": 2, "MODE": 8, "SW_UP": 9, "SW_DN": 10,
               "SDA": 38, "SCL": 41, "DIR_A": 39, "DIR_B": 40, "PWM": 42}
# SDA/SCL moved from GPIO12/13 (physical pins 18/19) to GPIO38/41
# (physical pins 35/38) - see conversation. Not a firmware-arbitrary
# choice: pins 18/19 sit in a part of U2's real footprint where the PCB
# is already at copper capacity (confirmed by both Freerouting and
# careful manual attempts failing to route out from there at all), while
# 35/38 sit immediately next to DIR_A/DIR_B/PWM (pins 36/37/39) - GPIOs
# that already route successfully from that exact neighborhood. Neither
# is strapping/PSRAM-reserved/native-USB (same constraints as before).
PIN = {sig: GPIO_PIN[g] for sig, g in SIGNAL_GPIO.items()}

OUT = {PIN["DIR_A"]: "DIR_A", PIN["DIR_B"]: "DIR_B", PIN["PWM"]: "PWM",
       PIN["MODE"]: None, PIN["KICK"]: "KICK", PIN["ISENSE"]: "ISENSE",
       PIN["SDA"]: "SDA", PIN["SCL"]: "SCL", PIN["SW_UP"]: "SW_UP",
       PIN["SW_DN"]: "SW_DN"}
pins = {k: s.pin("U1", k) for k in OUT}

# Every direct breakout off U2's own body gets the SAME stub length and
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# "left" pin's stub off to the right - as an earlier version of this did
# - drags the wire back across the entire 44-pin body, where it can run
# straight through another pin's own connection point and short onto
# whatever THAT pin carries (that's what happened to DIR_A/+5V and
# SW_DN/+3V3 here: a short ERC didn't have geometry to flag as
# "overlapping", since it's a wire passing through a pin tip, not two
# collinear segments). Each stub must exit on its pin's own side, and
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STUB_LEN = 20.0
# ISENSE isn't in this list - see the current-sense divider below, which
# wires straight to U2's own pin instead of a uniform stub+label.
RIGHT_SIDE = (PIN["KICK"], PIN["SW_UP"], PIN["SW_DN"],
              PIN["SDA"])
# SCL (GPIO41/pin38) is drawn on the symbol's LEFT side (checked directly
# against MCU.pins_by_unit, same as the DIR_A/DIR_B/PWM warning above -
# SDA's new pin (35) is still RIGHT_SIDE, SCL's isn't, they don't have to
# match each other).
LEFT_SIDE = (PIN["DIR_A"], PIN["DIR_B"], PIN["PWM"], PIN["SCL"])
for num in RIGHT_SIDE:
    p = pins[num]
    x = p[0] + STUB_LEN
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# stub or "spare" label, that only made sense when this pin was one of
# a handful the hand-drawn box even had.

# Current-sense divider (R4/R5), moved here next to U2's own ISENSE pin
# and wired to it with a literal wire - like the original, single-board
# schematic had it, before any of the off-board/pigtail experiments.
# U5 (the ACS current sensor) stays behind in SUPPLY/DRIVE, next to the
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# needs to cross the sheet now, so that end gets the matching label
# instead (the same swap made for every other signal that crosses a
# long distance on this sheet).
isense_pin = pins[PIN["ISENSE"]]
RX = isense_pin[0] + 35
# Standing (compact vertical) footprint, not this design's usual R_
# default - PCB-side only (the schematic symbol doesn't care about
# mounting style). Checked directly: on the real board these two sit in
# the K1-to-K2 corridor, which is only wide enough for U5's DIP-8 socket
# once R4/R5 stop taking up ~12mm of vertical run each for their leads.
FOOTPRINT_VERT_R = "Resistor_THT:R_Axial_DIN0207_L6.3mm_D2.5mm_P2.54mm_Vertical"
s.place(R_, "R1", "10k", RX, isense_pin[1] - 6.35, footprint=FOOTPRINT_VERT_R)
s.place(R_, "R2", "20k", RX, isense_pin[1] + 6.35, footprint=FOOTPRINT_VERT_R)
r4_top, r4_bot = s.pin("R1", "1"), s.pin("R1", "2")
r5_top, r5_bot = s.pin("R2", "1"), s.pin("R2", "2")
s.wire(r4_bot, r5_top)
# R4/R5 are centred on ISENSE's own row (isense_pin[1] == the midpoint
# of r4_bot/r5_top below), so the tap wire back to U2 is a single
# straight line, no jog needed.
tap_y = (r4_bot[1] + r5_top[1]) / 2
s.wire(isense_pin, (RX, tap_y))
s.junction((RX, tap_y))
s.wire(r4_top, (r4_top[0] + 12, r4_top[1]))
s.glabel("VIOUT", r4_top[0] + 12, r4_top[1])
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# free gap - this is the section that actually feeds that connector,
# so the two read as one visual unit.
s.note("HANDSET INTERFACE", 520, 300, 2.8)
# SW_UP/SW_DN/ISENSE arrive here as matching global labels off U2's own
# pins (see CONTROLLER above) - no physical pigtail connector in between
# any more now that U2 is on this board directly (JP4, the "sense
# pigtail" that used to sit here, is gone - see the note above). The
# column/rows below match where JP4's own pins used to land, purely so
# R11/R13/R14/R15/TB3/TB4 below don't have to move.
NODEX = {PIN["SW_UP"]: 540.0, PIN["SW_DN"]: 550.0}
SENSE_X0 = 524.51
SENSE_Y = {PIN["SW_UP"]: 339.09, PIN["SW_DN"]: 341.63}
jpsns2_pins = {}
for num in (PIN["SW_UP"], PIN["SW_DN"]):
    y = SENSE_Y[num]
    p = (SENSE_X0, y)
    # Wire from here to NODEX is drawn below, in the R11/R14 loop - not
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# HND_A/HND_B go there. TB4 pins point right, so +3V3/GND tap off to its
# right instead (no README circuit-number constraint here like TB1/TB2
# have, so sides are assigned for routing, not to match an external
# reference). Same row as SW_UP/R11 (pin 1 shares the 2.54mm pitch too),
# so no vertical nudge is needed to land it exactly.
s.place(TERM2, "TB1", "signal pair", 584.14, jpsns2_pins[PIN["SW_UP"]][1])
# mirror="y": TB4's wire goes right (to +3V3/GND), not left - unmirrored,
# its pins (and so its body) would sit on the wrong side, putting that
# wire through TB4 itself instead of clear of it. Moved right of where
# J3's own pin 3/4 column used to be, same reasoning as TB2.
s.place(TERM2, "TB2", "power pair", 599.59, jpsns2_pins[PIN["SW_UP"]][1],
        mirror="y")
for num, rs, tref, jn in ((PIN["SW_UP"], "R3", "TB1", "1"),
                          (PIN["SW_DN"], "R4", "TB1", "2")):
    p = jpsns2_pins[num]
    nx = NODEX[num]
    s.wire(p, (nx, p[1]))
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# an extra 8mm from a plain -3.81 (just clearing the row below) so the
# +3V3 tap wire above isn't stretched so much longer than the drop to
# the row below - was a 16.83mm run up vs. under 8mm down.
pullup_y = jpsns2_pins[PIN["SW_UP"]][1] - 3.81 - 8
for num, rp in ((PIN["SW_UP"], "R5"), (PIN["SW_DN"], "R6")):
    nx = NODEX[num]
    s.place(R_, rp, "100k", nx, pullup_y)
    # rtop (pin 1) sits ABOVE pin 2 (smaller y) - the +3V3 tap must go
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# INTERFACE section above the "HANDSET (unmodified)" box below it.
NOTE_TEXT = "handset sees 3V3 only - 29V never reaches it"
j3_cx = (s.pin("TB1", "1")[0] + s.pin("TB2", "1")[0]) / 2
note_y = jpsns2_pins[PIN["SW_UP"]][1] + 20
s.note(NOTE_TEXT, j3_cx - len(NOTE_TEXT) * 1.7 * 0.6 / 2, note_y, 1.7)

# ============================================ tof sensor prep (phase 2) ==
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# row, so that swap dragged those parts 37mm into each other and
# reintroduced shorts elsewhere. Leave this tuple's row values matching
# unit-number order.)
GATES = ((1, PIN["DIR_A"], "R8", 215), (2, PIN["DIR_B"], "R9", 255),
         (3, PIN["PWM"], "R10", 292))
# Q sits on the right, same side as the AND gates - it clears the body's
# height first before jogging to the shared WDOG column, same reasoning
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# for visual tidiness - the two buses don't overlap in Y.
WDX = BX
pq = s.pin("U2", "13", unit=1)
# WDOG wires to the top input pin below, not the bottom one - swapped
# from the name-matches-position default so WDOG (fed from a column left
# of everything) lands on top instead of bottom - so the bus needs that
# pin's offset, same for every unit (all three sit at the same py).
_, top_py = AND2.offset("1", unit=1)
last_a_y = GATES[-1][3] - top_py
s.wire(pq, (pq[0], pq[1] + 20), (WDX, pq[1] + 20), (WDX, last_a_y))
s.label("WDOG", WDX, pq[1] + 26)

# DIR_A/DIR_B/PWM all arrive here via a hand-soldered pigtail from U2's
# own header pins (see the MCU-side glabels above) now - stash their
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# PWM/KICK reach U3/U6 by matching label straight off U2's own stubs
# now, the same mechanism WDOG already uses, instead of routing to a
# JP5 pigtail connector that no longer represents a real board edge.
targets = [pa, gate_targets[PIN["DIR_A"]], gate_targets[PIN["DIR_B"]],
           gate_targets[PIN["PWM"]]]
labels = ["KICK", "DIR_A", "DIR_B", "PWM"]
for target, label in zip(targets, labels):
    x = target[0] - 8
    s.wire(target, (x, target[1]))
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s.wire((MRETX, s.pin("K1", "14")[1]), (MRETX, d5_bottom[1]))
# exactly on the vertical run (was offset +2 in x, off the wire and
# thus not actually connected to the net it names).
s.label("MRET", MRETX, d5_bottom[1] - 6)

# current sense sits to the right of K1 and below J2, clear of both,
# instead of sandwiched between them - real part puts VCC/GND top/
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# so a straight 2-point wire - a 3-point version with a now-coincident
# middle waypoint produced an invisible zero-length first segment.
s.wire(pk1, ip_minus)
s.label("DRV_UP", COMX["K1"], pk1[1])
ip_plus = s.pin("U4", "1")
pk2 = (COMX["K2"], s.pin("K2", "11")[1])

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# sheet, and wired to TB2.1 with a literal wire instead of a same-named
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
